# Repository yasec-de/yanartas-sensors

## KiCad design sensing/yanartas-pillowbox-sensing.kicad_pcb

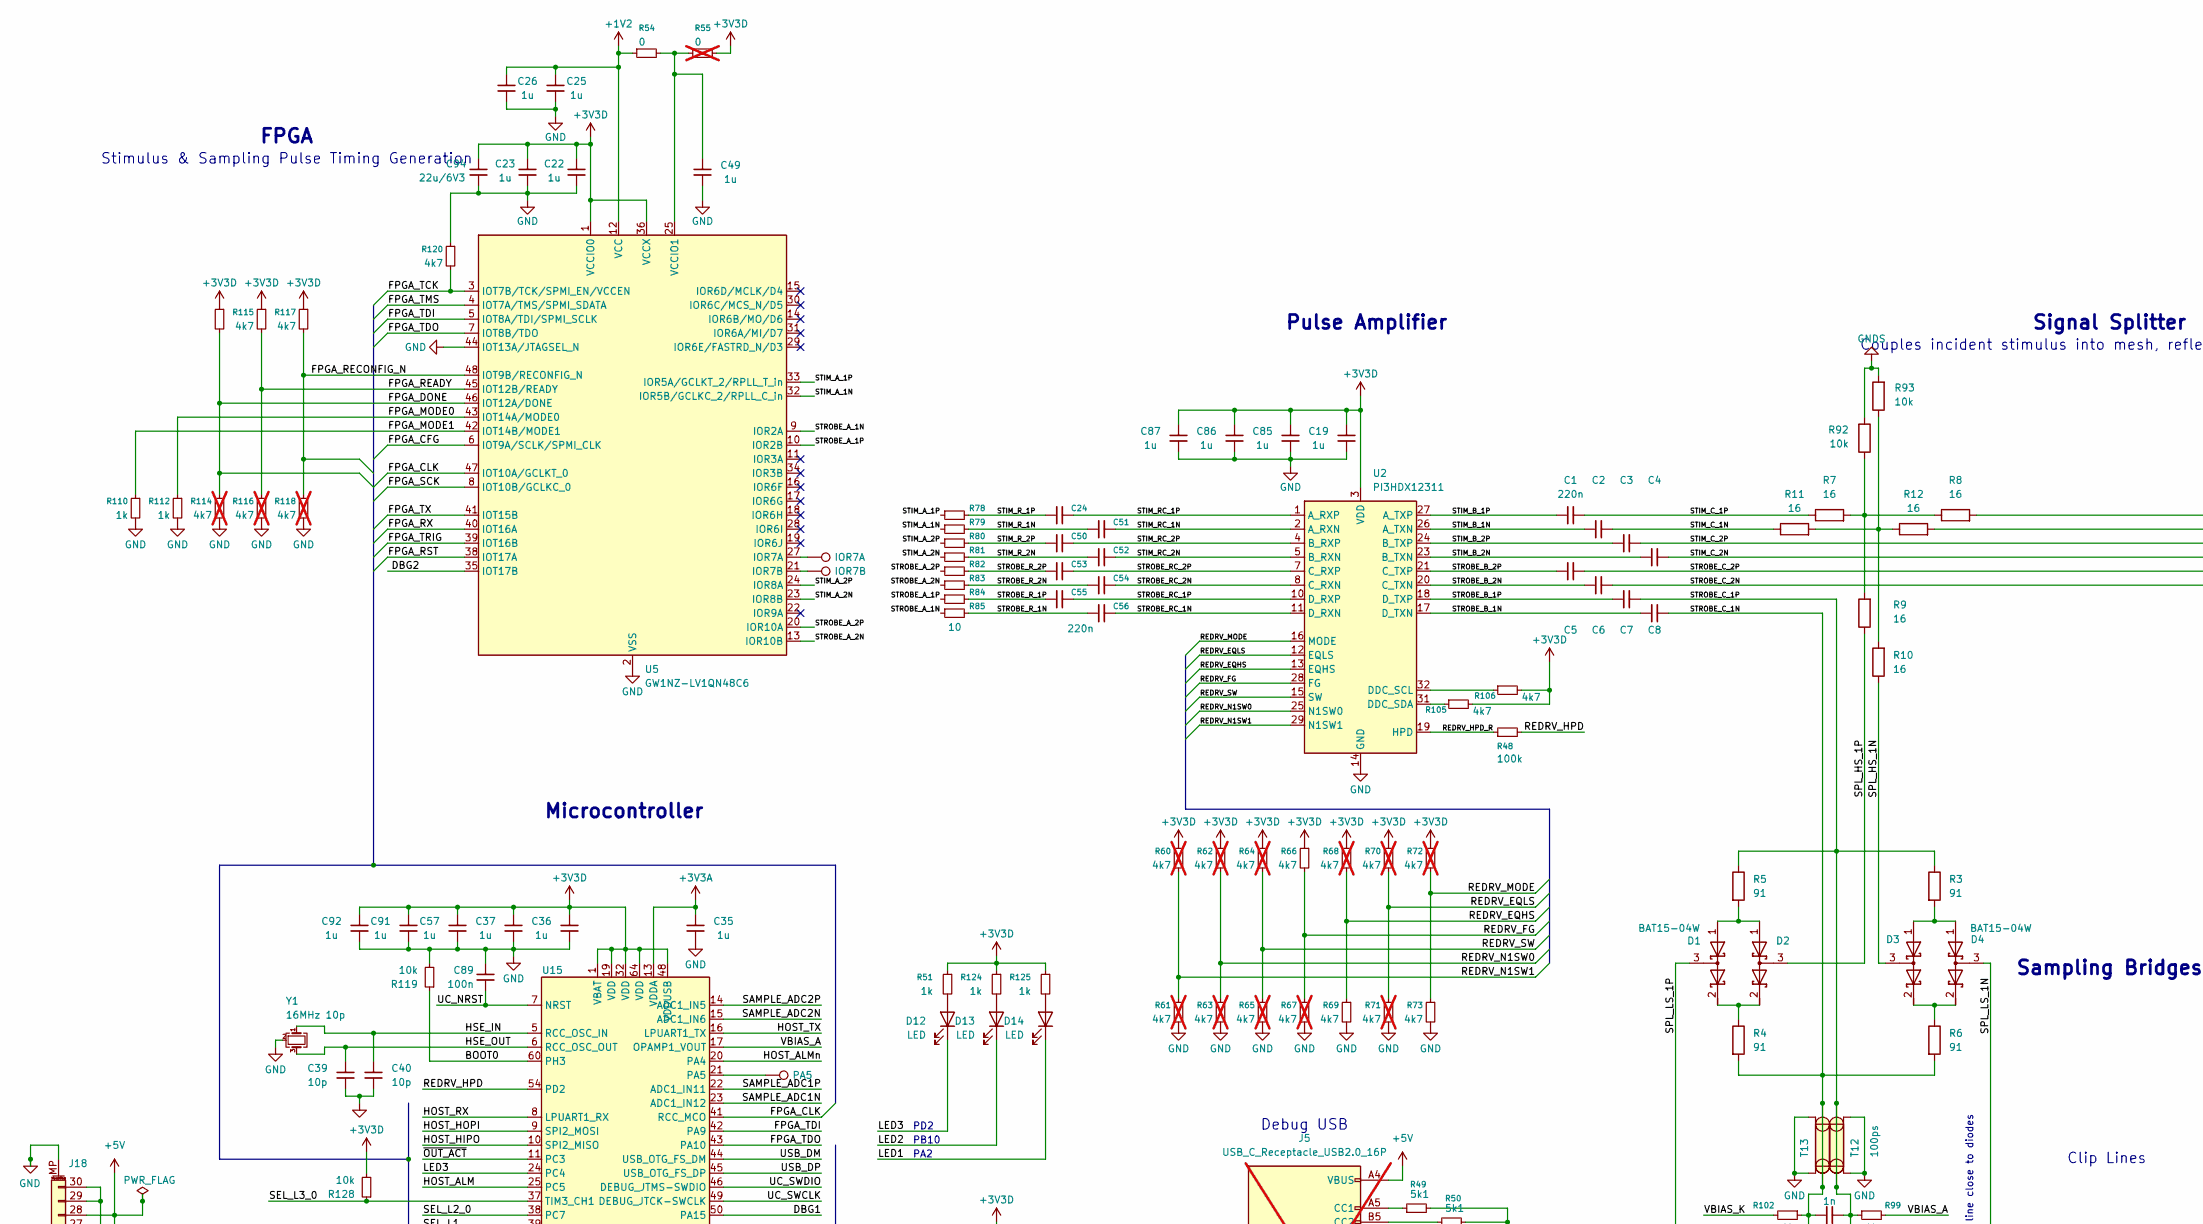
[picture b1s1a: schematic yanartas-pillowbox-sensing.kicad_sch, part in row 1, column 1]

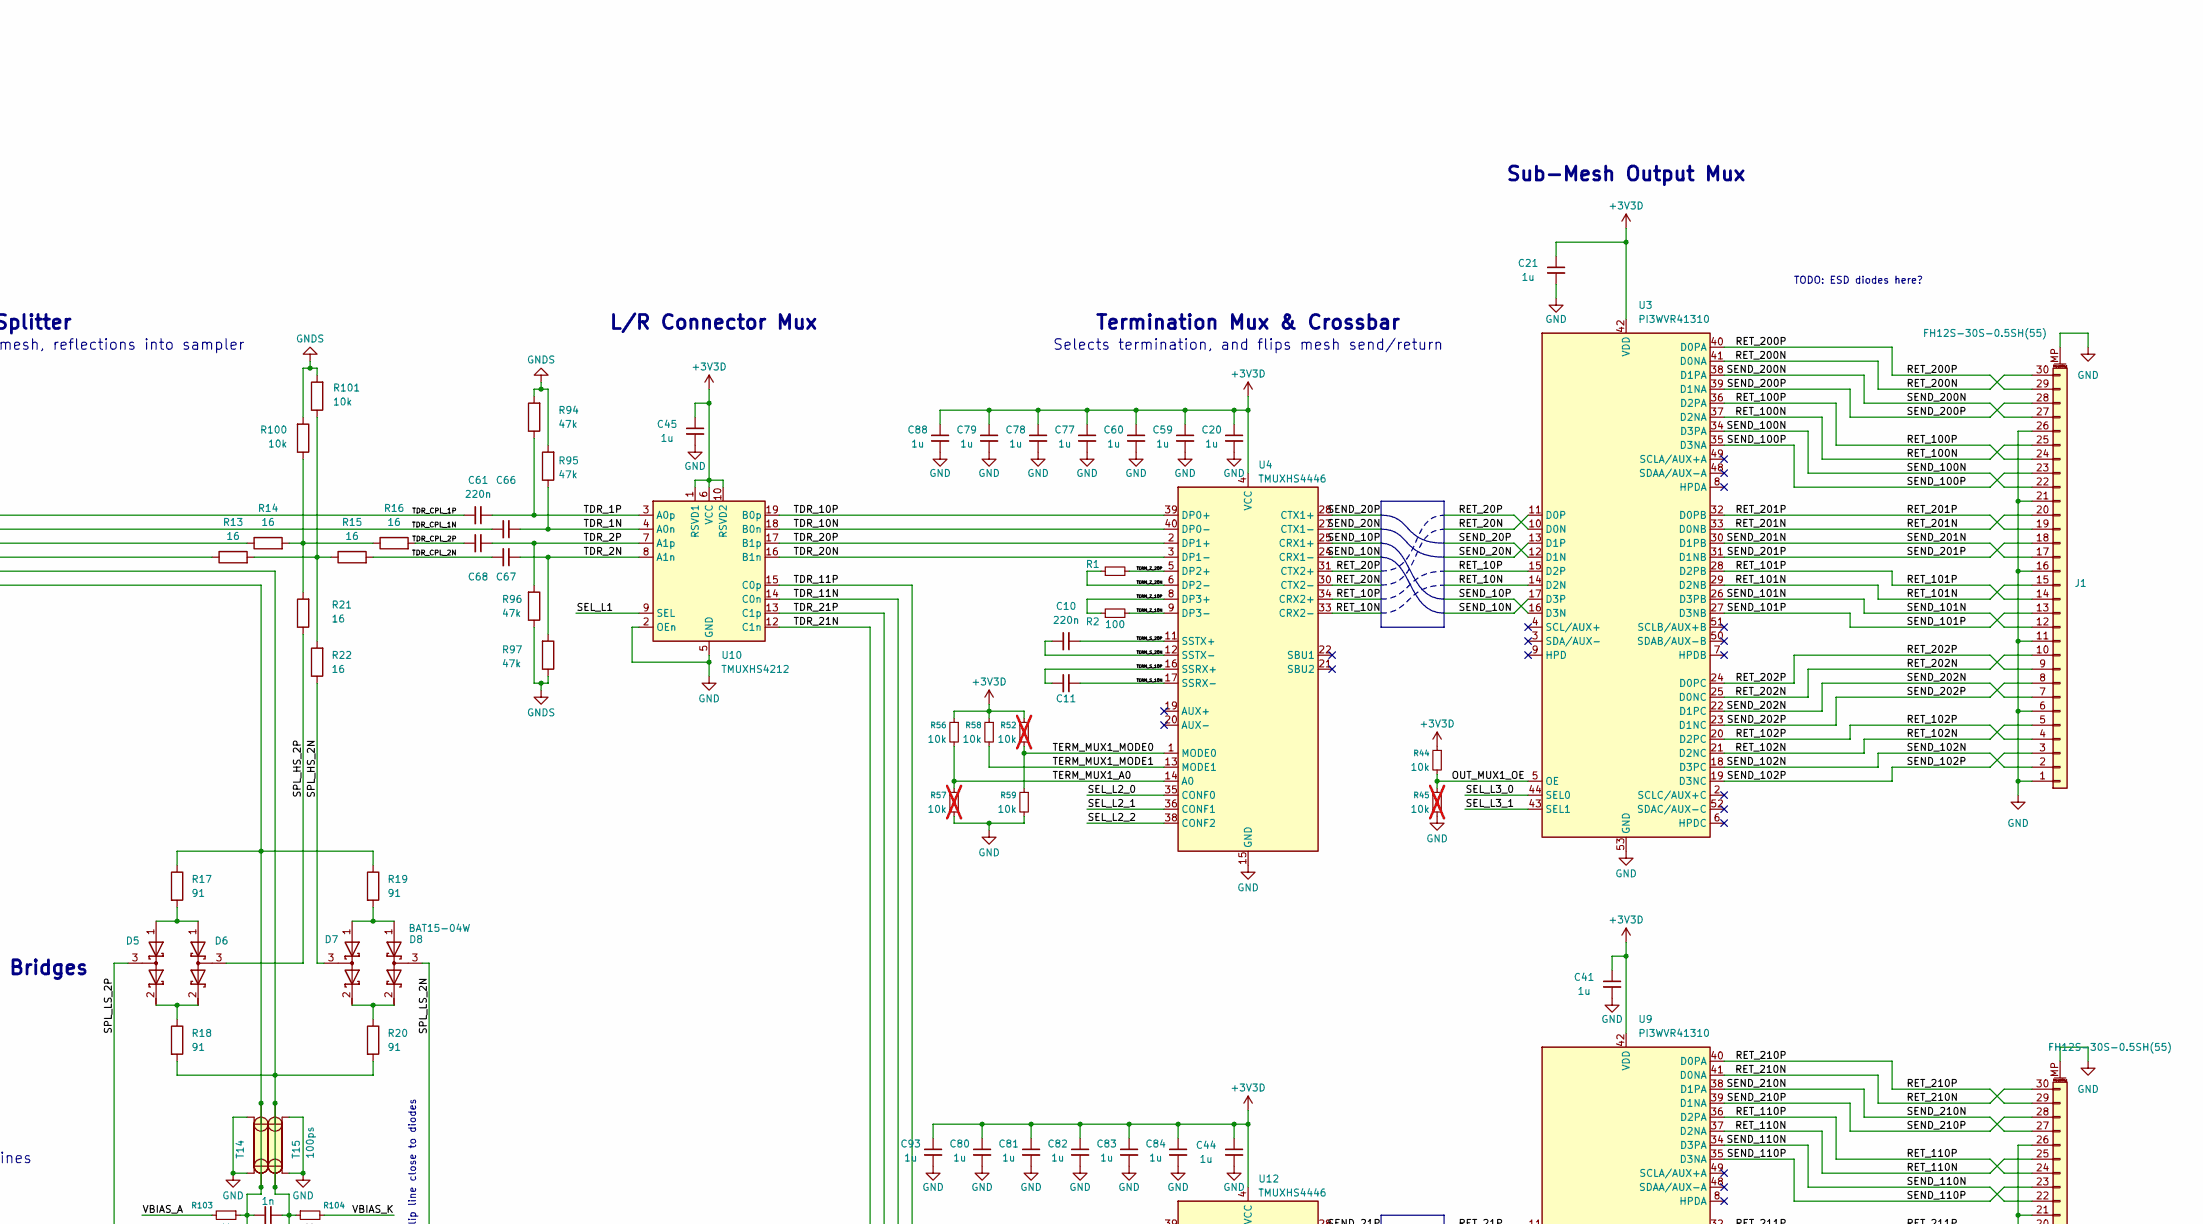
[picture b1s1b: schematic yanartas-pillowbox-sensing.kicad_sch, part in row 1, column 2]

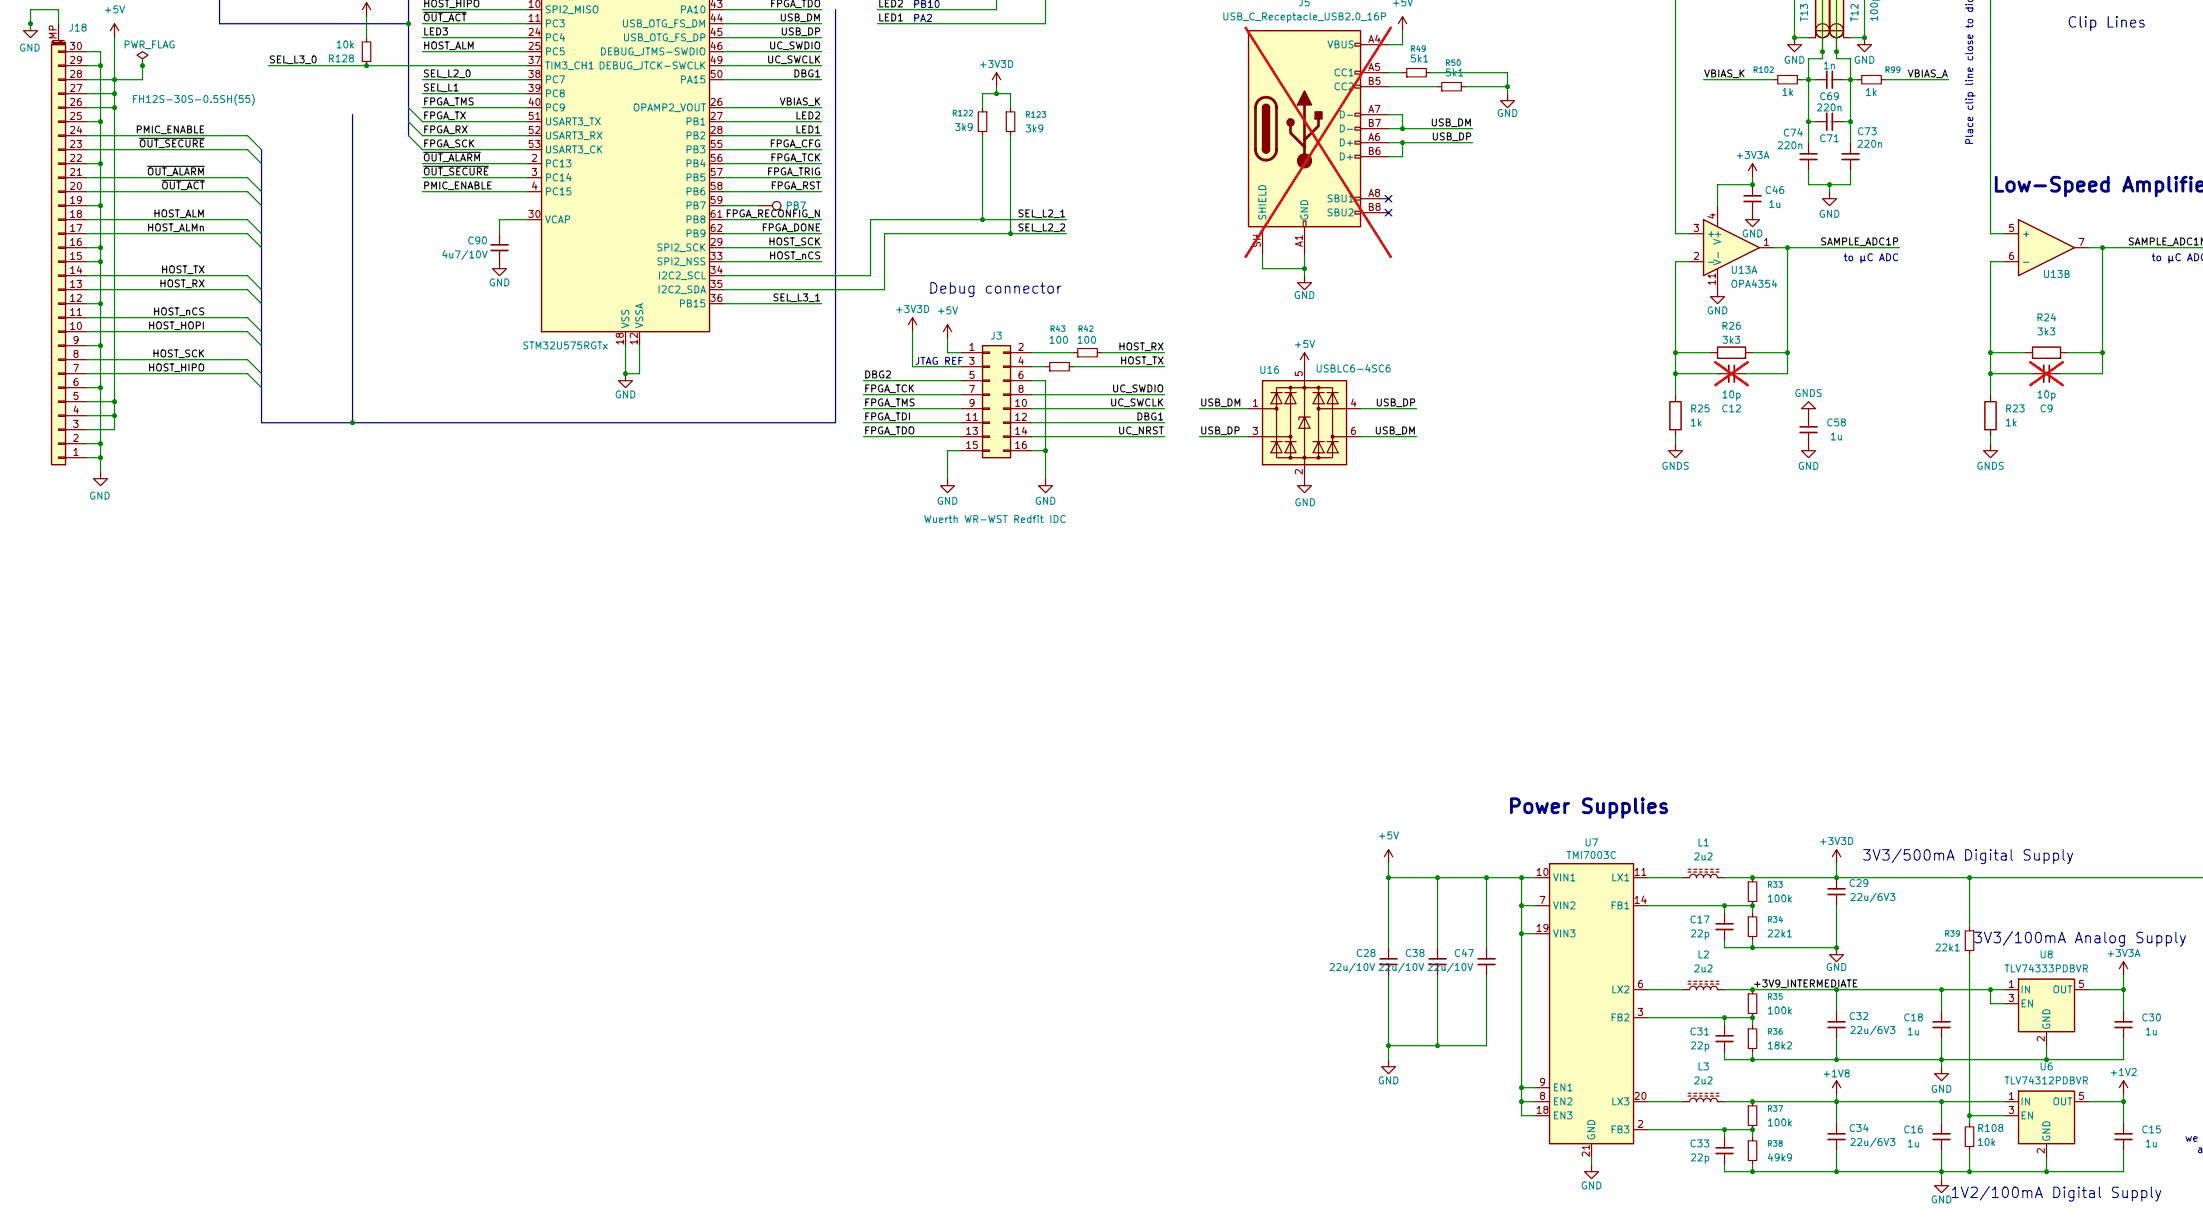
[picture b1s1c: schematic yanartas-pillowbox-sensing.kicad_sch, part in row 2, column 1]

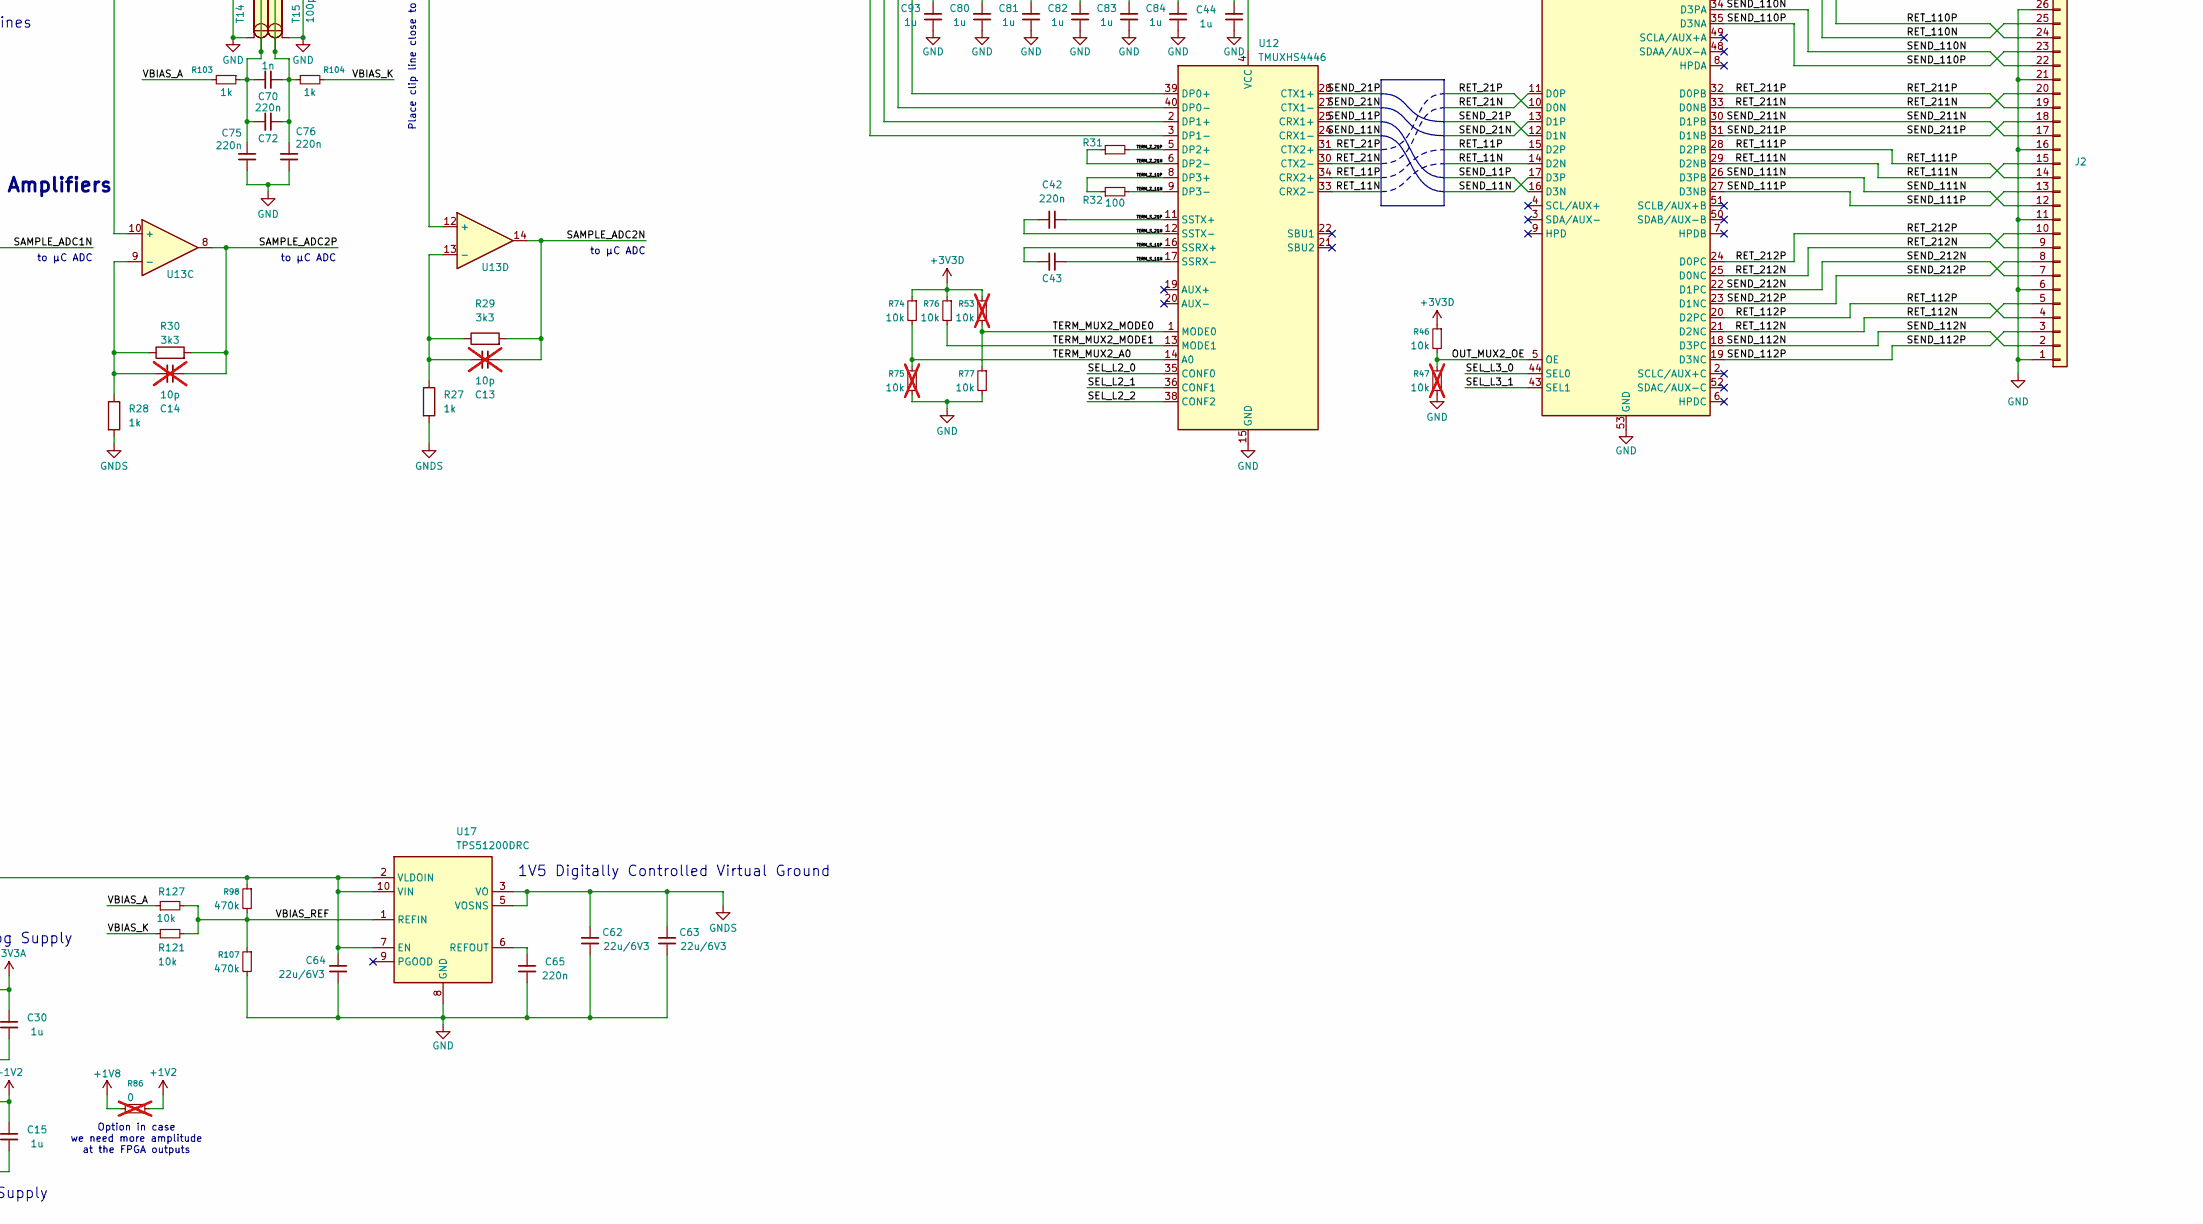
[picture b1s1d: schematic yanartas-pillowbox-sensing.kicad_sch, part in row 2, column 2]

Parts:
C1, C2, C3, C4, C5, C6, C7, C8, C10, C11, C24, C42, C43, C50, C51, C52, C53, C54, C55, C56, C61, C65, C66, C67, C68, C71, C72, C73, C74, C75, C76: 220n; C_0402_1005Metric; LCSC C16772
C9, C12, C13, C14: 10p; C_0402_1005Metric; LCSC C32949; not fitted
C15, C16, C18, C19, C20, C21, C22, C23, C25, C26, C30, C35, C36, C37, C41, C44, C45, C46, C49, C57, C58, C59, C60, C77, C78, C79, C80, C81, C82, C83, C84, C85, C86, C87, C88, C91, C92, C93: 1u; C_0402_1005Metric; LCSC C52923
C17, C31, C33: 22p; C_0402_1005Metric; LCSC C1555
C28, C38, C47: 22u/10V; C_0805_2012Metric; LCSC C45783
C29, C32, C34, C62, C63, C64, C94: 22u/6V3; C_0805_2012Metric; LCSC C45783
C39, C40: 10p; C_0402_1005Metric; LCSC C32949
C69, C70: 1n; C_0402_1005Metric; LCSC C1523
C89: 100n; C_0402_1005Metric; LCSC C1525
C90: 4u7/10V; C_0402_1005Metric; LCSC C23733
D1, D2, D3, D4, D5, D6, D7, D8: BAT15-04W; SOT-323_SC-70; LCSC C5380972
D12, D13, D14: LED; LED_0603_1608Metric; LCSC C2290
J1, J2, J18: FH12S-30S-0.5SH(55); Hirose_FH12-30S-0.5SH_1x30-1MP_P0.50mm_Horizontal; LCSC C3169607
J3: Wuerth WR-WST Redfit IDC; Würth_WR-WST_debug_490107671612_2x08_P2.54mm_Vertical; LCSC NA
J5: USB_C_Receptacle_USB2.0_16P; USB_C_Receptacle_HRO_TYPE-C-31-M-12; LCSC C165948; not fitted
L1, L2, L3: 2u2; CJIANG_FXL0420; LCSC C167206
R1, R2, R31, R32, R42, R43: 100; R_0402_1005Metric; LCSC C25076
R3, R4, R5, R6, R17, R18, R19, R20: 91; R_0402_1005Metric; LCSC C270574
R7, R8, R9, R10, R11, R12, R13, R14, R15, R16, R21, R22: 16; R_0402_1005Metric; LCSC C227309
R23, R25, R27, R28, R51, R99, R102, R103, R104, R110, R112, R124, R125: 1k; R_0402_1005Metric; LCSC C11702
R24, R26, R29, R30: 3k3; R_0402_1005Metric; LCSC C25890
R33, R35, R37, R48: 100k; R_0402_1005Metric; LCSC C25741
R34, R39: 22k1; R_0402_1005Metric; LCSC C43473
R36: 18k2; R_0402_1005Metric; LCSC C25859
R38: 49k9; R_0402_1005Metric; LCSC C25897
R44, R46, R56, R58, R59, R74, R76, R77, R92, R93, R100, R101, R108, R119, R121, R127, R128: 10k; R_0402_1005Metric; LCSC C25744
R45, R47, R52, R53, R57, R75: 10k; R_0402_1005Metric; LCSC C25744; not fitted
R49, R50: 5k1; R_0402_1005Metric; LCSC C25905
R54: 0; R_0402_1005Metric; LCSC C17168
R55, R86: 0; R_0402_1005Metric; LCSC C17168; not fitted
R60, R61, R62, R63, R64, R65, R67, R68, R70, R71, R72, R114, R116, R118: 4k7; R_0402_1005Metric; LCSC C25900; not fitted
R66, R69, R73, R105, R106, R113, R115, R117, R120: 4k7; R_0402_1005Metric; LCSC C25900
R78, R79, R80, R81, R82, R83, R84, R85: 10; R_0402_1005Metric; LCSC C25077
R94, R95, R96, R97: 47k; R_0402_1005Metric; LCSC C25792
R98, R107: 470k; R_0402_1005Metric; LCSC C25790
R122, R123: 3k9; R_0402_1005Metric; LCSC C51721
T12, T13, T14, T15: 100ps; LCSC NA
TP22: IOR7A; TestPoint_Pad_D1.0mm; LCSC NA
TP23: IOR7B; TestPoint_Pad_D1.0mm; LCSC NA
TP24: PA5; TestPoint_Pad_D1.0mm; LCSC NA
TP25: PB7; TestPoint_Pad_D1.0mm; LCSC NA
U2: PI3HDX12311; Diodes_XEA32_X1-QFN-32-1EP_2.85x4.5mm_P0.4mm_EP1.75x3.4mm; Digikey 31-PI3HDX12311XEAEXCT-ND
U3, U9: PI3WVR41310; Diodes_ZL52_TQFN-52-1EP_3.5x9mm_P0.4mm_EP2x7.5mm; Digikey 31-PI3WVR41310ZLEXCT-ND
U4, U12: TMUXHS4446; Texas_WQFN-40-1EP_3x6mm_P0.4mm_EP1.7x4.5mm; Digikey 296-TMUXHS4446IRETRCT-ND
U5: GW1NZ-LV1QN48C6; Gowin_QN48_QFN-48-1EP_6x6mm_P0.4mm_EP4.3x4.3mm; LCSC C5799569
U6: TLV74312PDBVR; SOT-23-5; LCSC C485149
U7: TMI7003C; QFN-20-1EP_3x3mm_P0.4mm_EP1.7x1.7mm; LCSC C840566
U8: TLV74333PDBVR; SOT-23-5; LCSC_Alt C408972
U10: TMUXHS4212; Texas_RKS0020A_VQFN-20-1EP_2.5x4.5mm_P0.5mm_EP1x3mm; LCSC C2869871
U13: OPA4354; TSSOP-14_4.4x5mm_P0.65mm; LCSC C527494
U15: STM32U575RGTx; LQFP-64_10x10mm_P0.5mm; Digikey 497-STM32U575RGT6TRCT-ND
U16: USBLC6-4SC6; SOT-23-6; LCSC C558419
U17: TPS51200DRC; VSON-10-1EP_3x3mm_P0.5mm_EP1.65x2.4mm; LCSC C34771
Y1: 16MHz 10p; Crystal_SMD_3225-4Pin_3.2x2.5mm; LCSC C13738

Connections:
+1V2: C15.2, C25.2, C26.2, R54.1, R86.2, U5.12 (VCC), U5.37 (VCC), U6.5 (OUT)
+1V8: C16.2, C34.2, L3.2, R37.1, R86.1, U6.1 (IN)
+3V3A: C30.2, C35.2, C46.2, U8.5 (OUT), U13.4 (V+), U15.13 (VDDA)
+3V3D: C19.2, C20.2, C21.2, C22.2, C23.2, C29.2, C36.2, C37.2, C41.2, C44.2, C45.2, C57.2, C59.2, C60.2, C64.2, C77.2, C78.2, C79.2, C80.2, C81.2, C82.2, C83.2, C84.2, C85.2, C86.2, C87.2, C88.2, C91.2, C92.2, C93.2, C94.2, J3.3, L1.2, R33.1, R39.1, R44.1, R46.1, R51.1, R52.1, R53.1, R55.2, R56.1, R58.1, R60.1, R62.1, R64.1, R66.1, R68.1, R70.1, R72.1, R74.1, R76.1, R98.1, R105.2, R106.2, R113.1, R115.1, R117.1, R122.1, R123.1, R124.1, R125.1, R128.2, U2.3 (VDD), U2.6 (VDD), U2.9 (VDD), U2.22 (VDD), U3.42 (VDD), U4.4 (VCC), U4.7 (VCC), U4.10 (VCC), U4.23 (VCC), U4.26 (VCC), U4.29 (VCC), U4.32 (VCC), U5.1 (VCCIO0), U5.36 (VCCX), U9.42 (VDD), U10.1 (RSVD1), U10.6 (VCC), U10.10 (RSVD2), U12.4 (VCC), U12.7 (VCC), U12.10 (VCC), U12.23 (VCC), U12.26 (VCC), U12.29 (VCC), U12.32 (VCC), U15.1 (VBAT), U15.19 (VDD), U15.32 (VDD), U15.48 (VDDUSB), U15.64 (VDD), U17.2 (VLDOIN), U17.7 (EN), U17.10 (VIN); also elsewhere on the board
+5V: C28.2, C38.2, C47.2, J3.1, J5.A4 (VBUS), J5.A9 (VBUS), J5.B4 (VBUS), J5.B9 (VBUS), J18.3, J18.4, J18.5, J18.26, J18.27, J18.28, U7.7 (VIN2), U7.8 (EN2), U7.9 (EN1), U7.10 (VIN1), U7.18 (EN3), U7.19 (VIN3), U16.5 (VBUS)
/+3V9_INTERMEDIATE: C18.2, C32.2, L2.2, R35.1, U8.1 (IN), U8.3 (EN)
/BOOT0: R119.1, U15.60 (PH3)
/DBG1: J3.12, U15.50 (PA15)
/DBG2: J3.5, U5.35 (IOT17B)
/FPGA_CFG: U5.6 (IOT9A/SCLK/SPMI_CLK), U15.55 (PB3)
/FPGA_CLK: U5.47 (IOT10A/GCLKT_0), U15.41 (RCC_MCO)
/FPGA_DONE: R113.2, R114.1, U5.46 (IOT12A/DONE), U15.62 (PB9)
/FPGA_MODE0: R112.1, U5.43 (IOT14A/MODE0); also elsewhere on the board
/FPGA_MODE1: R110.1, U5.42 (IOT14B/MODE1); also elsewhere on the board
/FPGA_READY: R115.2, R116.1, U5.45 (IOT12B/READY)
/FPGA_RECONFIG_N: R117.2, R118.1, U5.48 (IOT9B/RECONFIG_N), U15.61 (PB8)
/FPGA_RST: U5.38 (IOT17A), U15.58 (PB6)
/FPGA_RX: U5.40 (IOT16A), U15.52 (USART3_RX)
/FPGA_SCK: U5.8 (IOT10B/GCLKC_0), U15.53 (USART3_CK)
/FPGA_TCK: J3.7, R120.2, U5.3 (IOT7B/TCK/SPMI_EN/VCCEN), U15.56 (PB4)
/FPGA_TDI: J3.11, U5.5 (IOT8A/TDI/SPMI_SCLK), U15.42 (PA9)
/FPGA_TDO: J3.13, U5.7 (IOT8B/TDO), U15.43 (PA10)
/FPGA_TMS: J3.9, U5.4 (IOT7A/TMS/SPMI_SDATA), U15.40 (PC9)
/FPGA_TRIG: U5.39 (IOT16B), U15.57 (PB5)
/FPGA_TX: U5.41 (IOT15B), U15.51 (USART3_TX)
/HOST_ALM: J18.18, U15.25 (PC5)
/HOST_ALMn: J18.17, U15.20 (PA4)
/HOST_HIPO: J18.7, U15.10 (SPI2_MISO)
/HOST_HOPI: J18.10, U15.9 (SPI2_MOSI)
/HOST_RX: J18.13, R42.2, U15.8 (LPUART1_RX)
/HOST_SCK: J18.8, U15.29 (SPI2_SCK)
/HOST_TX: J18.14, R43.2, U15.16 (LPUART1_TX)
/HOST_nCS: J18.11, U15.33 (SPI2_NSS)
/HSE_IN: C40.2, U15.5 (RCC_OSC_IN), Y1.1
/HSE_OUT: C39.2, U15.6 (RCC_OSC_OUT), Y1.3
/LED1: D14.1 (K), U15.28 (PB2)
/LED2: D13.1 (K), U15.27 (PB1)
/LED3: D12.1 (K), U15.24 (PC4)
/OUT_MUX1_OE: R44.2, R45.1, U3.5 (OE)
/OUT_MUX2_OE: R46.2, R47.1, U9.5 (OE)
/PMIC_ENABLE: J18.24, U15.4 (PC15)
/REDRV_EQHS: R68.2, R69.1, U2.13 (EQHS)
/REDRV_EQLS: R70.2, R71.1, U2.12 (EQLS)
/REDRV_FG: R66.2, R67.1, U2.28 (FG)
/REDRV_HPD: R48.2, U15.54 (PD2)
/REDRV_HPD_R: R48.1, U2.19 (HPD)
/REDRV_MODE: R72.2, R73.1, U2.16 (MODE)
/REDRV_N1SW0: R62.2, R63.1, U2.25 (N1SW0)
/REDRV_N1SW1: R60.2, R61.1, U2.29 (N1SW1)
/REDRV_SW: R64.2, R65.1, U2.15 (SW)
/RET_10N: U3.14 (D2N), U4.33 (CRX2-)
/RET_10P: U3.15 (D2P), U4.34 (CRX2+)
/RET_11N: U9.14 (D2N), U12.33 (CRX2-)
/RET_11P: U9.15 (D2P), U12.34 (CRX2+)
/RET_20N: U3.11 (D0P), U4.30 (CTX2-)
/RET_20P: U3.10 (D0N), U4.31 (CTX2+)
/RET_21N: U9.11 (D0P), U12.30 (CTX2-)
/RET_21P: U9.10 (D0N), U12.31 (CTX2+)
/RET_100N: J1.25, U3.37 (D2NA)
/RET_100P: J1.24, U3.36 (D2PA)
/RET_101N: J1.15, U3.29 (D2NB)
/RET_101P: J1.14, U3.28 (D2PB)
/RET_102N: J1.5, U3.21 (D2NC)
/RET_102P: J1.4, U3.20 (D2PC)
/RET_110N: J2.25, U9.37 (D2NA)
/RET_110P: J2.24, U9.36 (D2PA)
/RET_111N: J2.15, U9.29 (D2NB)
/RET_111P: J2.14, U9.28 (D2PB)
/RET_112N: J2.5, U9.21 (D2NC)
/RET_112P: J2.4, U9.20 (D2PC)
/RET_200N: J1.30, U3.41 (D0NA)
/RET_200P: J1.29, U3.40 (D0PA)
/RET_201N: J1.20, U3.33 (D0NB)
/RET_201P: J1.19, U3.32 (D0PB)
/RET_202N: J1.10, U3.25 (D0NC)
/RET_202P: J1.9, U3.24 (D0PC)
/RET_210N: J2.30, U9.41 (D0NA)
/RET_210P: J2.29, U9.40 (D0PA)
/RET_211N: J2.20, U9.33 (D0NB)
/RET_211P: J2.19, U9.32 (D0PB)
/RET_212N: J2.10, U9.25 (D0NC)
/RET_212P: J2.9, U9.24 (D0PC)
/SAMPLE_ADC1N: C9.2, R24.2, U13.7, U15.23 (ADC1_IN12)
/SAMPLE_ADC1P: C12.2, R26.2, U13.1, U15.22 (ADC1_IN11)
/SAMPLE_ADC2N: C13.2, R29.2, U13.14, U15.15 (ADC1_IN6)
/SAMPLE_ADC2P: C14.2, R30.2, U13.8, U15.14 (ADC1_IN5)
/SEL_L1: U10.9 (SEL), U15.39 (PC8)
/SEL_L2_0: U4.35 (CONF0), U12.35 (CONF0), U15.38 (PC7)
/SEL_L2_1: R122.2, U4.36 (CONF1), U12.36 (CONF1), U15.34 (I2C2_SCL)
/SEL_L2_2: R123.2, U4.38 (CONF2), U12.38 (CONF2), U15.35 (I2C2_SDA)
/SEL_L3_0: R128.1, U3.44 (SEL0), U9.44 (SEL0), U15.37 (TIM3_CH1)
/SEL_L3_1: U3.43 (SEL1), U9.43 (SEL1), U15.36 (PB15)
/SEND_10N: U3.17 (D3P), U4.24 (CRX1-)
/SEND_10P: U3.16 (D3N), U4.25 (CRX1+)
/SEND_11N: U9.17 (D3P), U12.24 (CRX1-)
/SEND_11P: U9.16 (D3N), U12.25 (CRX1+)
/SEND_20N: U3.13 (D1P), U4.27 (CTX1-)
/SEND_20P: U3.12 (D1N), U4.28 (CTX1+)
/SEND_21N: U9.13 (D1P), U12.27 (CTX1-)
/SEND_21P: U9.12 (D1N), U12.28 (CTX1+)
/SEND_100N: J1.22, U3.34 (D3PA)
/SEND_100P: J1.23, U3.35 (D3NA)
/SEND_101N: J1.12, U3.26 (D3PB)
/SEND_101P: J1.13, U3.27 (D3NB)
/SEND_102N: J1.2, U3.18 (D3PC)
/SEND_102P: J1.3, U3.19 (D3NC)
/SEND_110N: J2.22, U9.34 (D3PA)
/SEND_110P: J2.23, U9.35 (D3NA)
/SEND_111N: J2.12, U9.26 (D3PB)
/SEND_111P: J2.13, U9.27 (D3NB)
/SEND_112N: J2.2, U9.18 (D3PC)
/SEND_112P: J2.3, U9.19 (D3NC)
/SEND_200N: J1.27, U3.38 (D1PA)
/SEND_200P: J1.28, U3.39 (D1NA)
/SEND_201N: J1.17, U3.30 (D1PB)
/SEND_201P: J1.18, U3.31 (D1NB)
/SEND_202N: J1.7, U3.22 (D1PC)
/SEND_202P: J1.8, U3.23 (D1NC)
/SEND_210N: J2.27, U9.38 (D1PA)
/SEND_210P: J2.28, U9.39 (D1NA)
/SEND_211N: J2.17, U9.30 (D1PB)
/SEND_211P: J2.18, U9.31 (D1NB)
/SEND_212N: J2.7, U9.22 (D1PC)
/SEND_212P: J2.8, U9.23 (D1NC)
/SPL_HS_1N: D3.3 (common), R10.1
/SPL_HS_1P: D2.3 (common), R9.1
/SPL_HS_2N: D7.3 (common), R22.1
/SPL_HS_2P: D6.3 (common), R21.1
/SPL_LS_1N: D4.3 (common), U13.5 (+)
/SPL_LS_1P: D1.3 (common), U13.3 (+)
/SPL_LS_2N: D8.3 (common), U13.12 (+)
/SPL_LS_2P: D5.3 (common), U13.10 (+)
/STIM_A_1N: R79.1, U5.32 (IOR5B/GCLKC_2/RPLL_C_in)
/STIM_A_1P: R78.1, U5.33 (IOR5A/GCLKT_2/RPLL_T_in)
/STIM_A_2N: R81.1, U5.23 (IOR8B)
/STIM_A_2P: R80.1, U5.24 (IOR8A)
/STIM_B_1N: C2.1, U2.26 (A_TXN)
/STIM_B_1P: C1.1, U2.27 (A_TXP)
/STIM_B_2N: C4.1, U2.23 (B_TXN)
/STIM_B_2P: C3.1, U2.24 (B_TXP)
/STIM_C_1N: C2.2, R11.1
/STIM_C_1P: C1.2, R7.1
/STIM_C_2N: C4.2, R13.1
/STIM_C_2P: C3.2, R14.1
/STIM_RC_1N: C51.2, U2.2 (A_RXN)
/STIM_RC_1P: C24.2, U2.1 (A_RXP)
/STIM_RC_2N: C52.2, U2.5 (B_RXN)
/STIM_RC_2P: C50.2, U2.4 (B_RXP)
/STIM_R_1N: C51.1, R79.2
/STIM_R_1P: C24.1, R78.2
/STIM_R_2N: C52.1, R81.2
/STIM_R_2P: C50.1, R80.2
/STROBE_A_1N: R85.1, U5.9 (IOR2A)
/STROBE_A_1P: R84.1, U5.10 (IOR2B)
/STROBE_A_2N: R83.1, U5.13 (IOR10B)
/STROBE_A_2P: R82.1, U5.20 (IOR10A)
/STROBE_B_1N: C8.1, U2.17 (D_TXN)
/STROBE_B_1P: C7.1, U2.18 (D_TXP)
/STROBE_B_2N: C6.1, U2.20 (C_TXN)
/STROBE_B_2P: C5.1, U2.21 (C_TXP)
/STROBE_C_1N: C8.2, C69.1, C71.1, C74.2, R4.2, R6.2, R102.1, T13.1, T13.3
/STROBE_C_1P: C7.2, C69.2, C71.2, C73.2, R3.1, R5.1, R99.1, T12.1, T12.3
/STROBE_C_2N: C6.2, C70.1, C72.1, C75.2, R17.1, R19.1, R103.1, T14.1, T14.3
/STROBE_C_2P: C5.2, C70.2, C72.2, C76.2, R18.2, R20.2, R104.1, T15.1, T15.3
/STROBE_RC_1N: C56.2, U2.11 (D_RXN)
/STROBE_RC_1P: C55.2, U2.10 (D_RXP)
/STROBE_RC_2N: C54.2, U2.8 (C_RXN)
/STROBE_RC_2P: C53.2, U2.7 (C_RXP)
/STROBE_R_1N: C56.1, R85.2
/STROBE_R_1P: C55.1, R84.2
/STROBE_R_2N: C54.1, R83.2
/STROBE_R_2P: C53.1, R82.2
/TDR_1N: C66.2, R95.1, U10.4 (A0n)
/TDR_1P: C61.2, R94.1, U10.3 (A0p)
/TDR_2N: C67.2, R97.2, U10.8 (A1n)
/TDR_2P: C68.2, R96.2, U10.7 (A1p)
/TDR_10N: U4.40 (DP0-), U10.18 (B0n)
/TDR_10P: U4.39 (DP0+), U10.19 (B0p)
/TDR_11N: U10.14 (C0n), U12.40 (DP0-)
/TDR_11P: U10.15 (C0p), U12.39 (DP0+)
/TDR_20N: U4.3 (DP1-), U10.16 (B1n)
/TDR_20P: U4.2 (DP1+), U10.17 (B1p)
/TDR_21N: U10.12 (C1n), U12.3 (DP1-)
/TDR_21P: U10.13 (C1p), U12.2 (DP1+)
/TDR_CPL_1N: C66.1, R12.2
/TDR_CPL_1P: C61.1, R8.2
/TDR_CPL_2N: C67.1, R15.2
/TDR_CPL_2P: C68.1, R16.2
/TERM_MUX1_A0: R56.2, R57.1, U4.14 (A0)
/TERM_MUX1_MODE0: R52.2, R59.1, U4.1 (MODE0)
/TERM_MUX1_MODE1: R58.2, U4.13 (MODE1)
/TERM_MUX2_A0: R74.2, R75.1, U12.14 (A0)
/TERM_MUX2_MODE0: R53.2, R77.1, U12.1 (MODE0)
/TERM_MUX2_MODE1: R76.2, U12.13 (MODE1)
/TERM_S_10N: C11.2, U4.17 (SSRX-)
/TERM_S_10P: C11.1, U4.16 (SSRX+)
/TERM_S_11N: C43.2, U12.17 (SSRX-)
/TERM_S_11P: C43.1, U12.16 (SSRX+)
/TERM_S_20N: C10.1, U4.12 (SSTX-)
/TERM_S_20P: C10.2, U4.11 (SSTX+)
/TERM_S_21N: C42.1, U12.12 (SSTX-)
/TERM_S_21P: C42.2, U12.11 (SSTX+)
/TERM_Z_10N: R2.2, U4.9 (DP3-)
/TERM_Z_10P: R2.1, U4.8 (DP3+)
/TERM_Z_11N: R32.2, U12.9 (DP3-)
/TERM_Z_11P: R32.1, U12.8 (DP3+)
/TERM_Z_20N: R1.1, U4.6 (DP2-)
/TERM_Z_20P: R1.2, U4.5 (DP2+)
/TERM_Z_21N: R31.1, U12.6 (DP2-)
/TERM_Z_21P: R31.2, U12.5 (DP2+)
/UC_NRST: C89.2, J3.14, U15.7 (NRST)
/UC_SWCLK: J3.10, U15.49 (DEBUG_JTCK-SWCLK)
/UC_SWDIO: J3.8, U15.46 (DEBUG_JTMS-SWDIO)
/USB_DM: J5.A7 (D-), J5.B7 (D-), U15.44 (USB_OTG_FS_DM), U16.1 (I/O1), U16.6 (I/O4)
/USB_DP: J5.A6 (D+), J5.B6 (D+), U15.45 (USB_OTG_FS_DP), U16.3 (I/O2), U16.4 (I/O3)
/VBIAS_A: R99.2, R103.2, R127.1, U15.17 (OPAMP1_VOUT)
/VBIAS_K: R102.2, R104.2, R121.1, U15.26 (OPAMP2_VOUT)
/VBIAS_REF: R98.2, R107.1, R121.2, R127.2, U17.1 (REFIN)
/~OUT_ACT: J18.20, U15.11 (PC3)
/~OUT_ALARM: J18.21, U15.2 (PC13)
/~OUT_SECURE: J18.23, U15.3 (PC14)
GND: C15.1, C16.1, C17.2, C18.1, C19.1, C20.1, C21.1, C22.1, C23.1, C25.1, C26.1, C28.1, C29.1, C30.1, C31.2, C32.1, C33.2, C34.1, C35.1, C36.1, C37.1, C38.1, C39.1, C40.1, C41.1, C44.1, C45.1, C46.1, C47.1, C49.1, C57.1, C58.1, C59.1, C60.1, C62.1, C63.1, C64.1, C65.1, C73.1, C74.1, C75.1, C76.1, C77.1, C78.1, C79.1, C80.1, C81.1, C82.1, C83.1, C84.1, C85.1, C86.1, C87.1, C88.1, C89.1, C90.2, C91.1, C92.1, C93.1, C94.1, J1.1, J1.6, J1.11, J1.16, J1.21, J1.26, J1.MP (MountPin), J2.1, J2.6, J2.11, J2.16, J2.21, J2.26, J2.MP (MountPin), J3.6, J3.15, J3.16, J5.A1 (GND), J5.A12 (GND), J5.B1 (GND), J5.B12 (GND), J5.SH (SHIELD), J18.1, J18.2, J18.6, J18.9, J18.12, J18.15, J18.16, J18.19, J18.22, J18.25, J18.29, J18.30, J18.MP (MountPin), R34.2, R36.2, R38.2, R45.2, R47.2, R49.2, R50.2, R57.2, R59.2, R61.2, R63.2, R65.2, R67.2, R69.2, R71.2, R73.2, R75.2, R77.2, R107.2, R108.1, R110.2, R112.2, R114.2, R116.2, R118.2, R119.2, R120.1, T12.2, T12.4, T13.2, T13.4, T14.2, T14.4, T15.2, T15.4, U2.14 (GND), U2.30 (GND), U2.33 (GND), U3.53 (GND), U4.15 (GND), U4.18 (GND), U4.37 (GND), U4.41 (GND), U5.2 (VSS), U5.26 (VSS), U5.44 (IOT13A/JTAGSEL_N), U5.49 (VSS), U6.2 (GND), U7.21 (GND), U8.2 (GND), U9.53 (GND), U10.2 (OEn), U10.5 (GND), U10.11 (GND), U10.20 (GND), U10.21 (GND), U12.15 (GND), U12.18 (GND), U12.37 (GND), U12.41 (GND), U13.11 (V-), U15.12 (VSSA), U15.18 (VSS), U15.31 (VSS), U15.47 (VSS), U15.63 (VSS), U16.2 (GND), U17.4 (GND), U17.8 (GND), U17.11 (GND), Y1.2 (G), Y1.4 (G)
GNDS: C58.2, C62.2, C63.2, R23.2, R25.2, R27.2, R28.2, R92.2, R93.2, R94.2, R95.2, R96.1, R97.1, R100.2, R101.2, U17.3 (VO), U17.5 (VOSNS)
unnamed: D1.1 (A), D2.1 (A), R5.2
unnamed: D1.2 (K), D2.2 (K), R4.1
unnamed: D3.1 (A), D4.1 (A), R3.2
unnamed: D3.2 (K), D4.2 (K), R6.1
unnamed: D5.1 (A), D6.1 (A), R17.2
unnamed: D5.2 (K), D6.2 (K), R18.1
unnamed: D7.1 (A), D8.1 (A), R19.2
unnamed: D7.2 (K), D8.2 (K), R20.1
unnamed: D12.2 (A), R51.2
unnamed: D13.2 (A), R124.2
unnamed: D14.2 (A), R125.2
unnamed: J3.2, R42.1
unnamed: J3.4, R43.1
unnamed: J5.A5 (CC1), R49.1
unnamed: J5.B5 (CC2), R50.1
unnamed: R7.2, R8.1, R9.2, R92.1
unnamed: R10.2, R11.2, R12.1, R93.1
unnamed: R14.2, R16.1, R21.2, R100.1
unnamed: R13.2, R15.1, R22.2, R101.1
unnamed: R106.1, U2.32 (DDC_SCL)
unnamed: R105.1, U2.31 (DDC_SDA)
unnamed: TP22.1 (1_1), U5.27 (IOR7A)
unnamed: TP23.1 (1_1), U5.21 (IOR7B)
unnamed: C49.2, R54.2, R55.1, U5.25 (VCCIO1)
unnamed: R39.2, R108.2, U6.3 (EN)
unnamed: C17.1, R33.2, R34.1, U7.14 (FB1)
unnamed: C31.1, R35.2, R36.1, U7.3 (FB2)
unnamed: C33.1, R37.2, R38.1, U7.2 (FB3)
unnamed: L1.1, U7.11 (LX1)
unnamed: L2.1, U7.6 (LX2)
unnamed: L3.1, U7.20 (LX3)
unnamed: C12.1, R25.1, R26.1, U13.2 (-)
unnamed: C9.1, R23.1, R24.1, U13.6 (-)
unnamed: C14.1, R28.1, R30.1, U13.9 (-)
unnamed: C13.1, R27.1, R29.1, U13.13 (-)
unnamed: TP24.1 (1_1), U15.21 (PA5)
unnamed: TP25.1 (1_1), U15.59 (PB7)
unnamed: C90.1, U15.30 (VCAP)
unnamed: C65.2, U17.6 (REFOUT)

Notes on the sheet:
Selects termination, and flips mesh send/return
to µC ADC
3V3/500mA Digital Supply
Place clip line close to diodes
Signal Splitter
Stimulus & Sampling Pulse Timing Generation
Sub-Mesh Output Mux
Debug connector
Power Supplies
PB10
Sampling Bridges
Pulse Amplifier
Option in case we need more amplitude at the FPGA outputs
PA2
TODO: ESD diodes here?
Debug USB
1V2/100mA Digital Supply
1V5 Digitally Controlled Virtual Ground
Low-Speed Amplifiers
FPGA
Termination Mux & Crossbar
3V3/100mA Analog Supply
Clip Lines
JTAG REF
Microcontroller
L/R Connector Mux
Couples incident stimulus into mesh, reflections into sampler
PD2

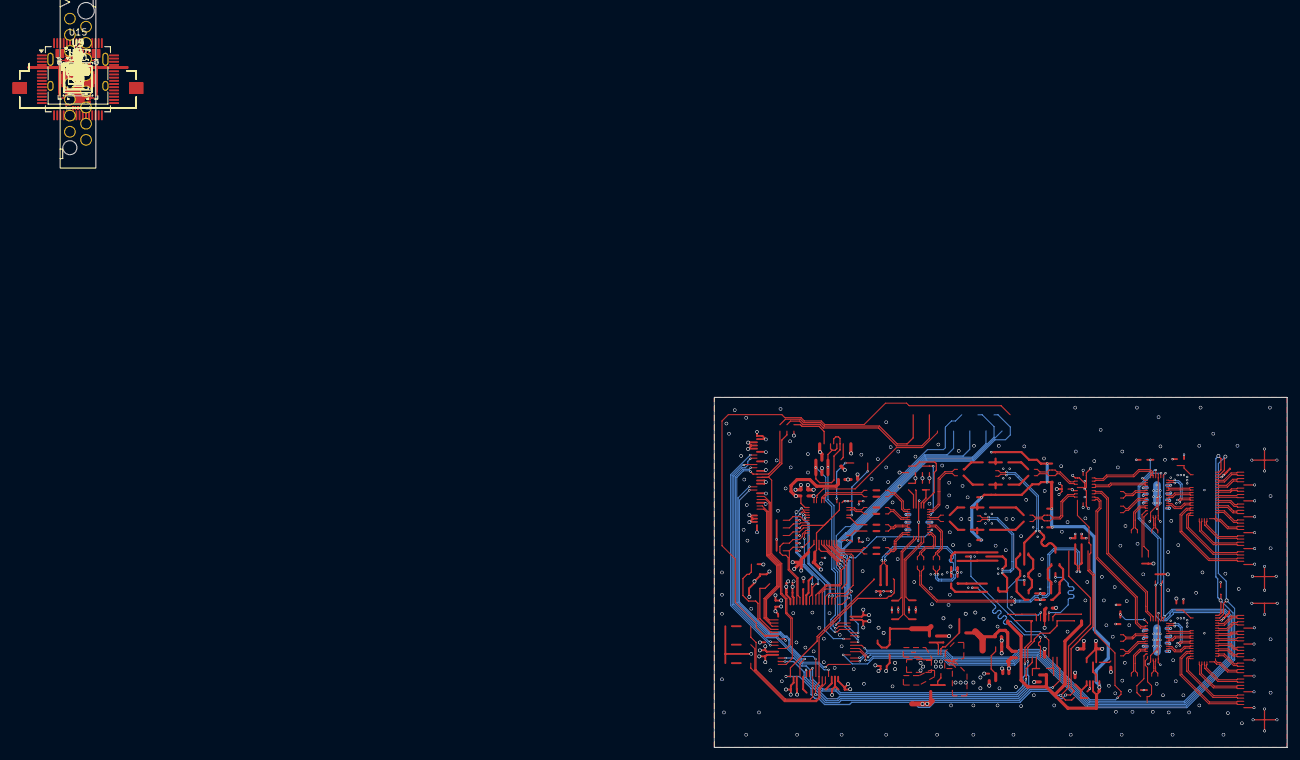
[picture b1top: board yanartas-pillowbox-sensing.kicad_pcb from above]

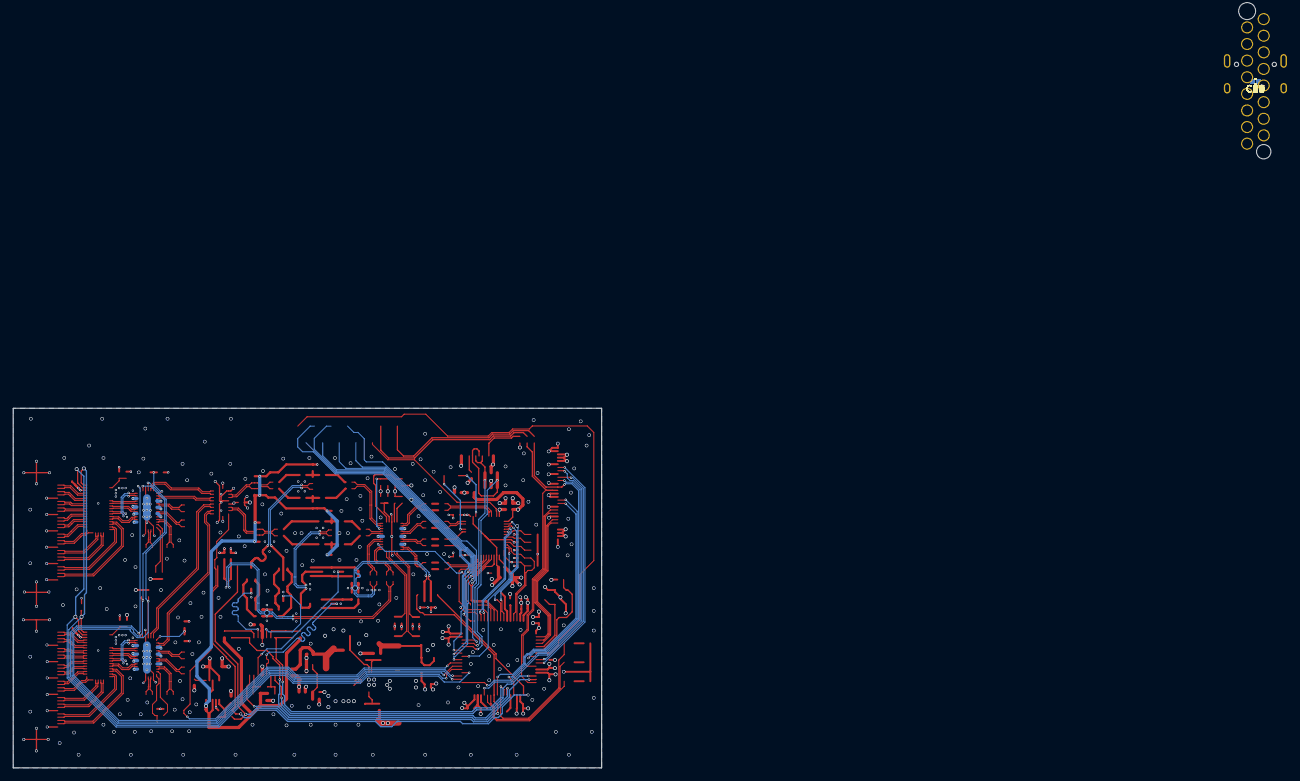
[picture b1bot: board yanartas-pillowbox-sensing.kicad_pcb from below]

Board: 4 copper layers, 90.0 x 55.0 mm, 250 parts (18 on the bottom side), 262 nets.

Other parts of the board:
R109, R111: 4k7; R_0402_1005Metric

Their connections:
+3V3D: R109.1, R111.1; also elsewhere on the board
/FPGA_MODE0: R111.2; also elsewhere on the board
/FPGA_MODE1: R109.2; also elsewhere on the board
